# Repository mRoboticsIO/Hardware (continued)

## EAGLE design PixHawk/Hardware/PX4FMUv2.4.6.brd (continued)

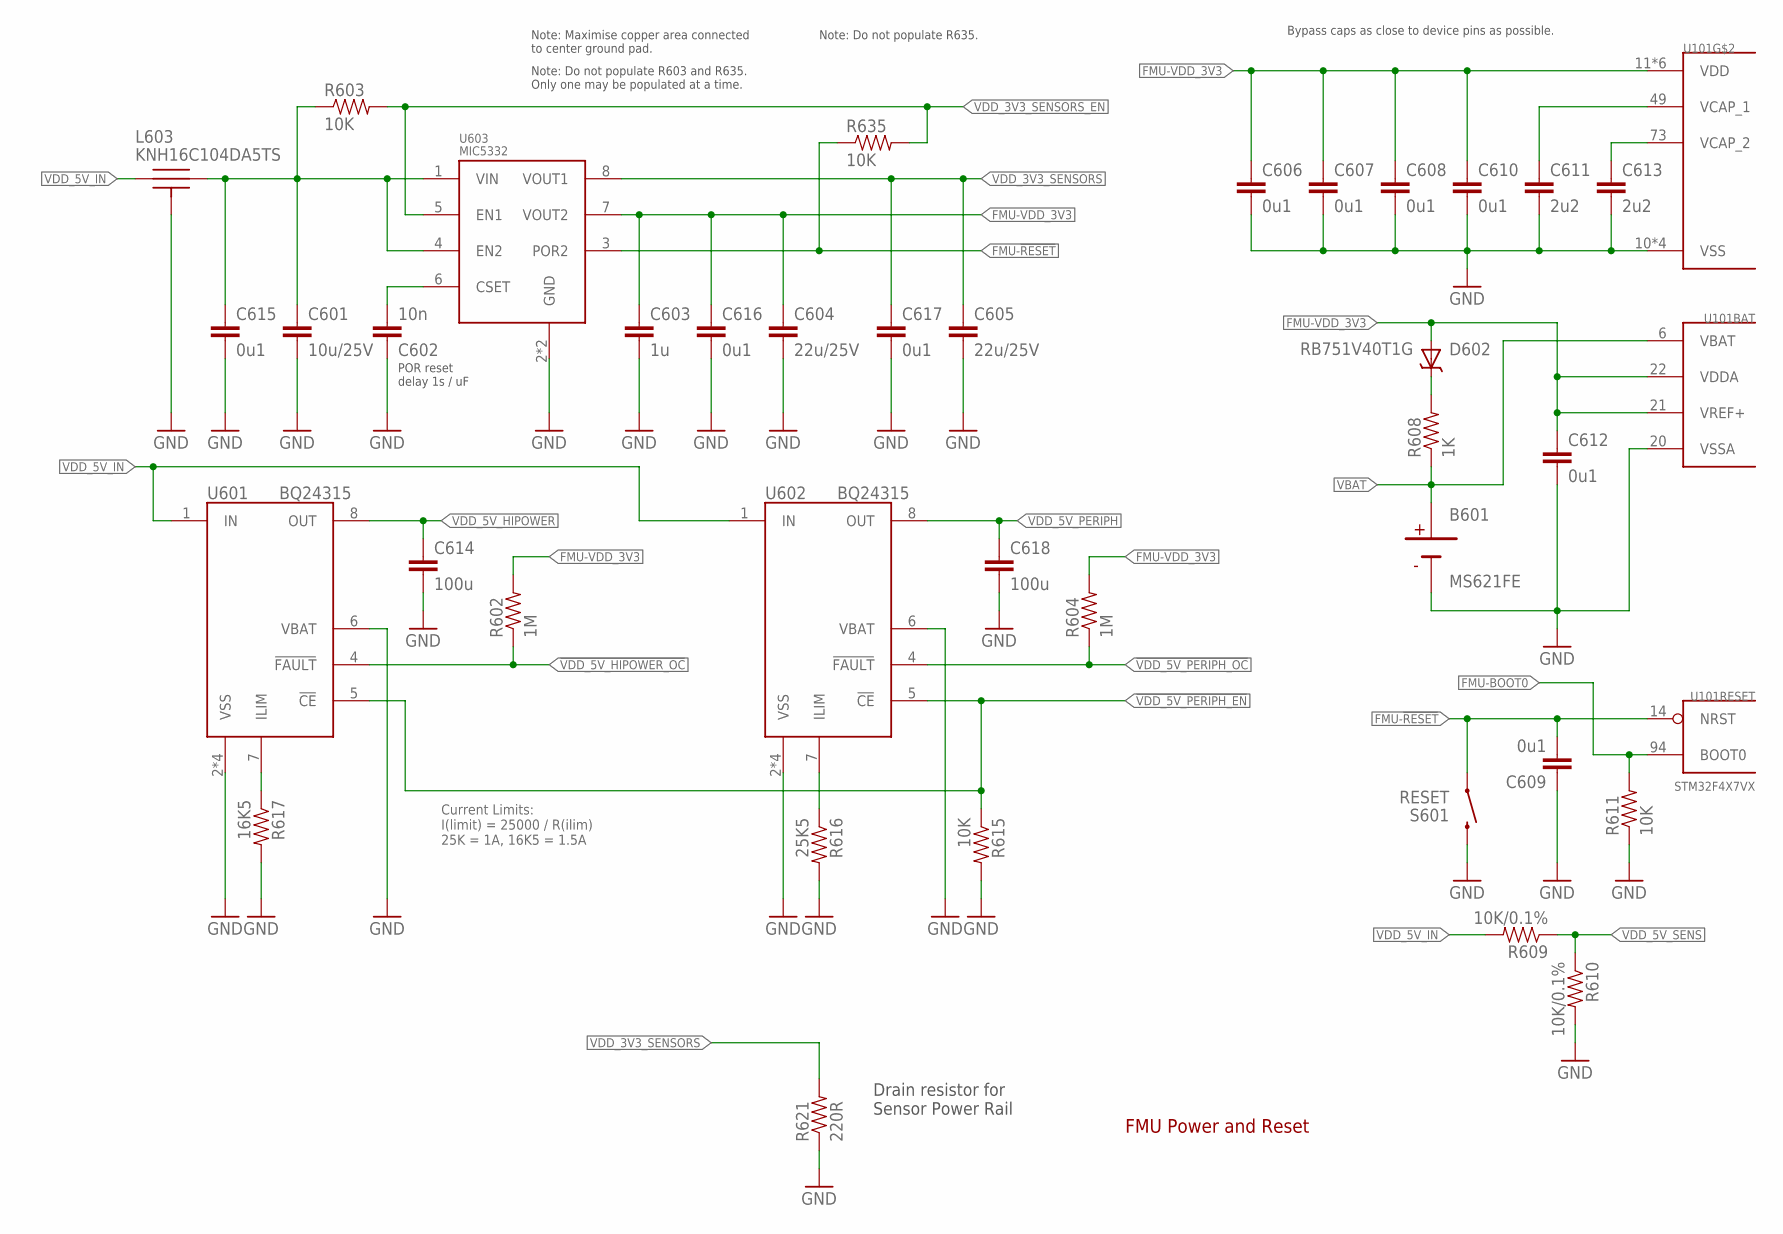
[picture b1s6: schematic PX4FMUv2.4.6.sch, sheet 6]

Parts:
B601: MS621FE; PARTNO MS621FE-FL11E
C601: 10u/25V; 0805-CAP; PARTNO CL21A106KAYNNNE
C602: 10n; 0402-CAP; PARTNO CC0402KRX7R7BB103
C603: 1u; 0603-CAP; PARTNO CC0603ZRY5V7BB105
C604, C605: 22u/25V; 0805-CAP; PARTNO CL21A226MAQNNNE
C606, C607, C608, C609, C610, C612, C615, C616, C617: 0u1; 0402-CAP; PARTNO CC0402ZRY5V7BB104
C611, C613: 2u2; 0603-CAP; PARTNO C1608X6S1C225K080AC
C614, C618: 100u; 1206-CAP; PARTNO C3216X5R1A107M160AC
D602: RB751V40T1G; SOD323; PARTNO RB751V40T1G
L603: KNH16C104DA5TS; KYOCERA-KNH16-DA; PARTNO KNH16C104DA5TS
R602, R604: 1M; 0402-RES; PARTNO RC0402FR-071ML
R603, R611, R615, R635: 10K; 0402-RES; PARTNO RC0402FR-0710KL
R608: 1K; 0402-RES; PARTNO RC0402FR-071KL
R609, R610: 10K/0.1%; 0402-RES; PARTNO ERA-2AEB103X
R616: 25K5; 0402-RES; PARTNO RMCF0402FT25K5
R617: 16K5; 0402-RES; PARTNO RMCF0402FT16K5
R621: 220R; 0603-RES; PARTNO RC1608J100CS
S601: RESET; EVQP7J01K; PARTNO EVQ-P7J01P
U101: STM32F4X7VX; TQFP100; PARTNO STM32F427VI
U601, U602: BQ24315; QFN8-DSG; PARTNO BQ24315DSGR
U603: MIC5332; MLF-8-EPAD; PARTNO MIC5332-SSYMT

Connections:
!VDD_5V_HIPOWER_OC: R602.P$1 (1), U601.4 (!FAULT); also elsewhere on the board
!VDD_5V_PERIPH_EN: R615.P$1 (1), U601.5 (!CE), U602.5 (!CE); also elsewhere on the board
!VDD_5V_PERIPH_OC: R604.P$1 (1), U602.4 (!FAULT); also elsewhere on the board
FMU-!RESET: C609.P$2 (2), R635.P$1 (1), S601.A1 (1), U101.14 (NRST), U603.3 (POR2); also elsewhere on the board
FMU-BOOT0: R611.P$2 (2), U101.94 (BOOT0); also elsewhere on the board
FMU-VDD_3V3: C603.P$1 (1), C604.P$1 (1), C606.P$1 (1), C607.P$1 (1), C608.P$1 (1), C610.P$1 (1), C612.P$1 (1), C616.P$1 (1), D602.A, R602.P$2 (2), R604.P$2 (2), U101.11 (VDD), U101.19 (VDD), U101.21 (VREF+), U101.22 (VDDA), U101.28 (VDD), U101.50 (VDD), U101.75 (VDD), U101.100 (VDD), U603.7 (VOUT2); also elsewhere on the board
FMU-VDD_5V5: C601.P$1 (1), C615.P$1 (1), L603.P$2, R603.P$1 (1), U603.1 (VIN), U603.4 (EN2)
GND: B601.2 (NEG), C601.P$2 (2), C602.P$1 (1), C603.P$2 (2), C604.P$2 (2), C605.P$2 (2), C606.P$2 (2), C607.P$2 (2), C608.P$2 (2), C609.P$1 (1), C610.P$2 (2), C611.P$2 (2), C612.P$2 (2), C613.P$2 (2), C614.P$2 (2), C615.P$2 (2), C616.P$2 (2), C617.P$2 (2), C618.P$2 (2), L603.P$3, L603.P$4, L603.P$5, R610.P$2 (2), R611.P$1 (1), R615.P$2 (2), R616.P$2 (2), R617.P$2 (2), R621.1, S601.B3 (2), U101.10 (VSS), U101.20 (VSSA), U101.27 (VSS), U101.74 (VSS), U101.99 (VSS), U601.2 (VSS), U601.6 (VBAT), U601.GND (VSS), U601.P$2 (VSS), U601.P$3 (VSS), U602.2 (VSS), U602.6 (VBAT), U602.GND (VSS), U602.P$2 (VSS), U602.P$3 (VSS), U603.2 (GND), U603.GND; also elsewhere on the board
unnamed: C613.P$1 (1), U101.73 (VCAP_2)
unnamed: C602.P$2 (2), U603.6 (CSET)
unnamed: C611.P$1 (1), U101.49 (VCAP_1)
unnamed: D602.C, R608.P$2 (2)
unnamed: R616.P$1 (1), U602.7 (ILIM)
unnamed: R617.P$1 (1), U601.7 (ILIM)
VBAT: B601.1 (POS), R608.P$1 (1), U101.6 (VBAT); also elsewhere on the board
VDD_3V3_SENSORS: C605.P$1 (1), C617.P$1 (1), R621.2, U603.8 (VOUT1); also elsewhere on the board
VDD_3V3_SENSORS_EN: R603.P$2 (2), R635.P$2 (2), U603.5 (EN1); also elsewhere on the board
VDD_5V_HIPOWER: C614.P$1 (1), U601.8 (OUT); also elsewhere on the board
VDD_5V_IN: L603.P$1, R609.P$2 (2), U601.1 (IN), U602.1 (IN); also elsewhere on the board
VDD_5V_PERIPH: C618.P$1 (1), U602.8 (OUT); also elsewhere on the board
VDD_5V_SENS: R609.P$1 (1), R610.P$1 (1); also elsewhere on the board

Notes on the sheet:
FMU Power and Reset
Bypass caps as close to device pins as possible.
Note: Maximise copper area connected to center ground pad.
POR reset delay 1s / uF
Current Limits: I(limit) = 25000 / R(ilim) 25K = 1A, 16K5 = 1.5A
Drain resistor for Sensor Power Rail
Note: Do not populate R603 and R635. Only one may be populated at a time.
Note: Do not populate R635.

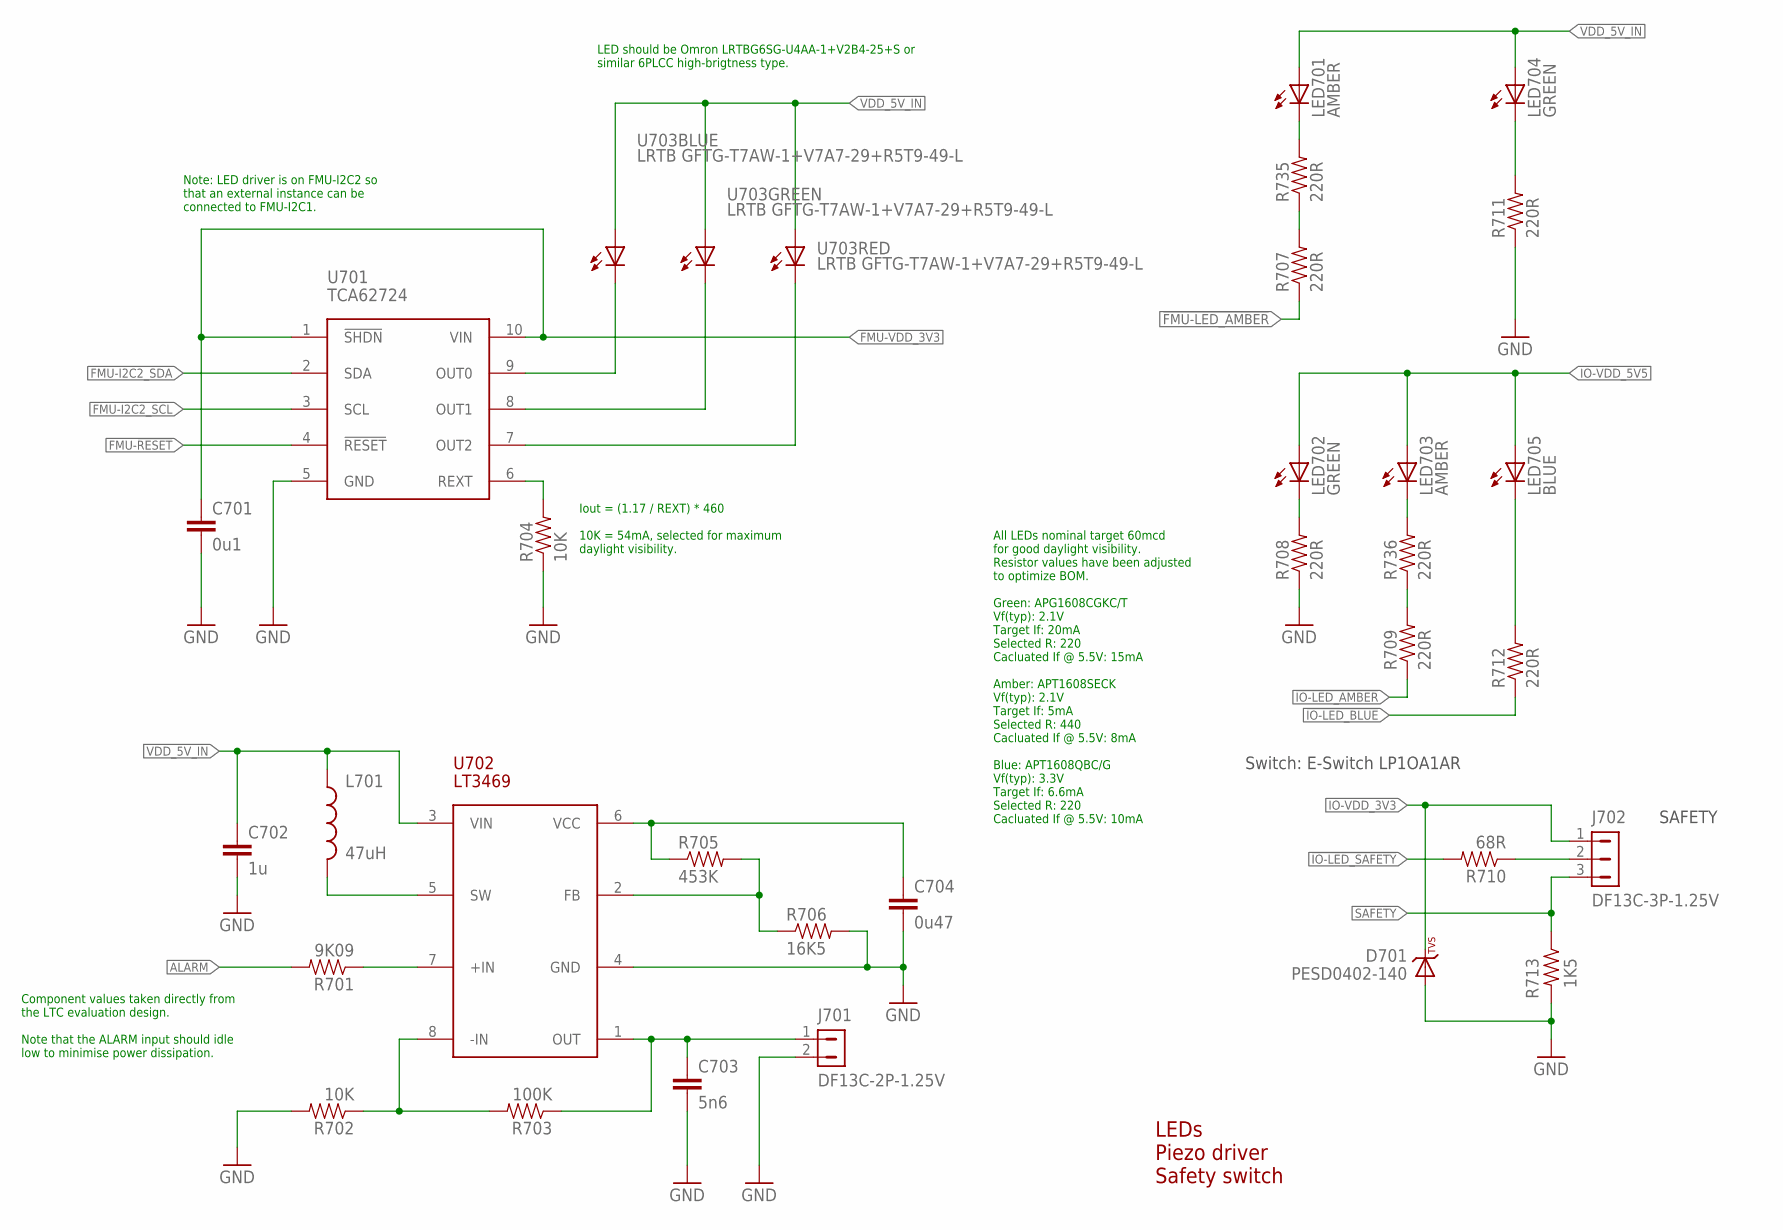
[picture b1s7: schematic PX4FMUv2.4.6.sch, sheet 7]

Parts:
C701: 0u1; 0402-CAP; PARTNO CC0402ZRY5V7BB104
C702: 1u; 0603-CAP; PARTNO CC0603ZRY5V7BB105
C703: 5n6; 0402-CAP; PARTNO C0402C562K5RACTU
C704: 0u47; 0402-CAP; PARTNO C1005X5R1C474K050BC
D701: PESD0402-140; 0402-TVS; PARTNO PESD0402-140
J701: DF13C-2P-1.25V; PARTNO DF13C-2P-1.25V(20)
J702: DF13C-3P-1.25V; PARTNO DF13C-3P-1.25V(20)
L701: 47uH; 0805-IND; PARTNO MLZ2012M470W
LED701, LED703: AMBER; 0603-LED; PARTNO APTD1608SECK
LED702, LED704: GREEN; 0603-LED; PARTNO APTD1608CGCK
LED705: BLUE; 0603-LED; PARTNO APTD1608QBC/D
R701: 9K09; 0402-RES; PARTNO RMCF0402FT9K09
R702, R704: 10K; 0402-RES; PARTNO RC0402FR-0710KL
R703: 100K; 0402-RES; PARTNO RC0402FR-07100KL
R705: 453K; 0402-RES; PARTNO RMCF0402FT453K
R706: 16K5; 0402-RES; PARTNO RMCF0402FT16K5
R707, R708, R709, R711, R712, R735, R736: 220R; 0402-RES; PARTNO RC0402FR-07220RL
R710: 68R; 0402-RES; PARTNO ERJ-2GEJ680X
R713: 1K5; 0402-RES; PARTNO RC0402FR-071K5L
U701: TCA62724FMG; SON10; PARTNO TCA62724FMG
U702: LT3469; SOT23-8; PARTNO LT3469ETS8
U703: LRTB GFTG-T7AW-1+V7A7-29+R5T9-49-L; 6-PLCC; PARTNO LRTB GFTG-T7AW-1+V7A7-29+R5T9-49-L

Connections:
!FMU-LED_AMBER: R707.P$1 (1); also elsewhere on the board
!IO-LED_AMBER: R709.P$1 (1); also elsewhere on the board
!IO-LED_BLUE: R712.P$1 (1); also elsewhere on the board
!IO-LED_SAFETY: R710.P$2 (2); also elsewhere on the board
ALARM: R701.P$2 (2); also elsewhere on the board
FMU-!RESET: U701.4 (!RESET); also elsewhere on the board
FMU-I2C2_SCL: U701.3 (SCL); also elsewhere on the board
FMU-I2C2_SDA: U701.2 (SDA); also elsewhere on the board
FMU-VDD_3V3: C701.P$1 (1), U701.1 (!SHDN), U701.10 (VIN); also elsewhere on the board
GND: C701.P$2 (2), C702.P$2 (2), C703.P$2 (2), C704.P$2 (2), D701.A, J701.2, R702.P$2 (2), R704.P$1 (1), R706.P$2 (2), R708.P$1 (1), R711.P$1 (1), R713.P$2 (2), U701.5 (GND), U702.4 (GND); also elsewhere on the board
IO-VDD_3V3: D701.C, J702.1; also elsewhere on the board
IO-VDD_5V5: LED702.A, LED703.A, LED705.A; also elsewhere on the board
unnamed: LED704.C, R711.P$2 (2)
unnamed: LED705.C, R712.P$2 (2)
unnamed: R707.P$2 (2), R735.P$1 (1)
unnamed: R705.P$2 (2), R706.P$1 (1), U702.2 (FB)
unnamed: R702.P$1 (1), R703.P$2 (2), U702.8 (-IN)
unnamed: LED701.C, R735.P$2 (2)
unnamed: C703.P$1 (1), J701.1, R703.P$1 (1), U702.1 (OUT)
unnamed: R701.P$1 (1), U702.7 (+IN)
unnamed: LED702.C, R708.P$2 (2)
unnamed: L701.P$2 (2), U702.5 (SW)
unnamed: C704.P$1 (1), R705.P$1 (1), U702.6 (VCC)
unnamed: R709.P$2 (2), R736.P$1 (1)
unnamed: LED703.C, R736.P$2 (2)
unnamed: J702.2, R710.P$1 (1)
unnamed: R704.P$2 (2), U701.6 (REXT)
RGB_LED_3: U701.9 (OUT0), U703.C1 (C)
RGB_LED_4: U701.8 (OUT1), U703.C2 (C)
RGB_LED_14: U701.7 (OUT2), U703.C3 (C)
SAFETY: J702.3, R713.P$1 (1); also elsewhere on the board
VDD_5V_IN: C702.P$1 (1), L701.P$1 (1), LED701.A, LED704.A, U702.3 (VIN), U703.A1 (A), U703.A2 (A), U703.A3 (A); also elsewhere on the board

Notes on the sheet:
LEDs Piezo driver Safety switch
Switch: E-Switch LP1OA1AR
SAFETY
LED should be Omron LRTBG6SG-U4AA-1+V2B4-25+S or similar 6PLCC high-brigtness type.
Iout = (1.17 / REXT) * 460 10K = 54mA, selected for maximum daylight visibility.
Note: LED driver is on FMU-I2C2 so that an external instance can be connected to FMU-I2C1.
All LEDs nominal target 60mcd for good daylight visibility. Resistor values have been adjusted to optimize BOM. Green: APG1608CGKC/T Vf(typ): 2.1V Target If: 20mA Selected R: 220 Cacluated If @ 5.5V: 15mA Amber: APT1608SECK Vf(typ): 2.1V Target If: 5mA Selected R: 440 Cacluated If @ 5.5V: 8mA Blue: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
Component values taken directly from the LTC evaluation design. Note that the ALARM input should idle low to minimise power dissipation.

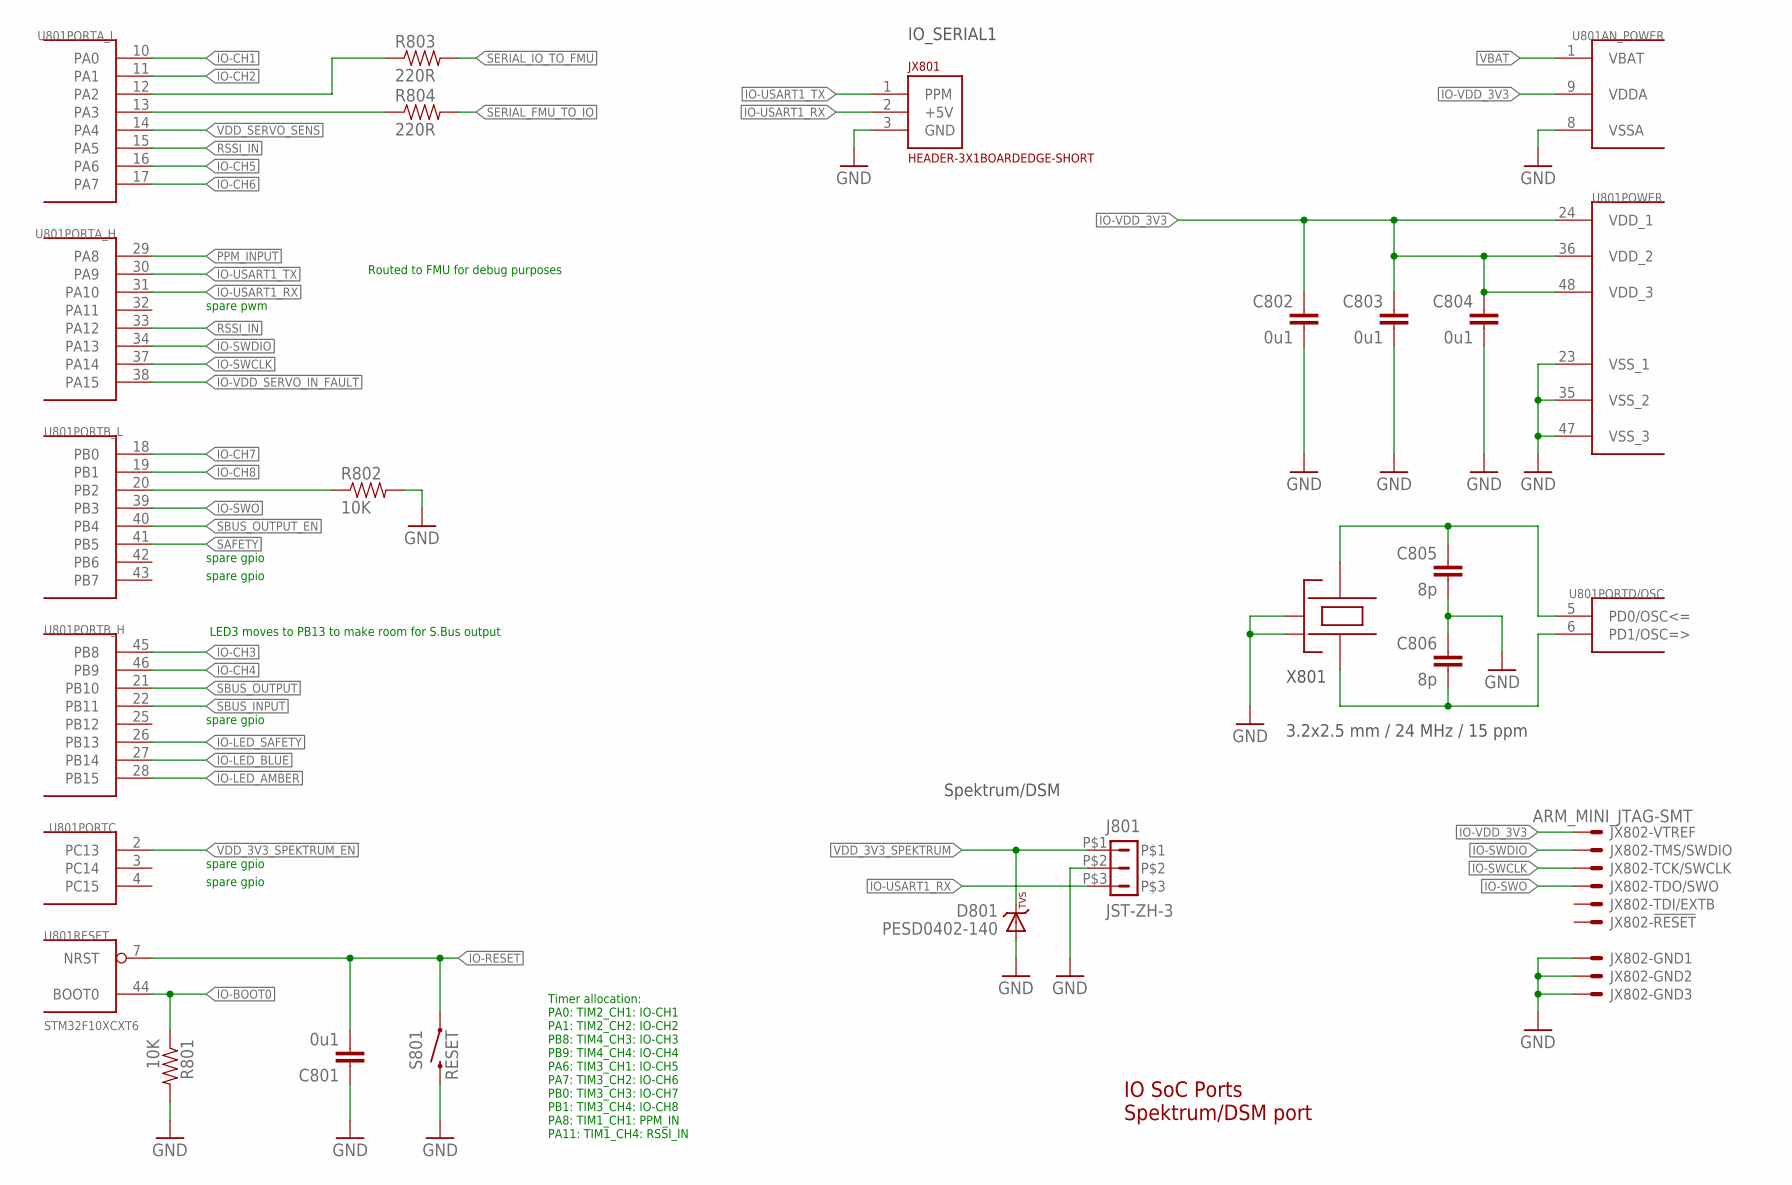
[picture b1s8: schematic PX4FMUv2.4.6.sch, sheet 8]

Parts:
C801, C802, C803, C804: 0u1; 0402-CAP; PARTNO CC0402ZRY5V7BB104
C805, C806: 8p; 0402-CAP; PARTNO C1005C0G1H080C
D801: PESD0402-140; 0402-TVS; PARTNO PESD0402-140
J801: JST-ZH-3; JST-ZH-SMT-VERTICAL; PARTNO B3B-ZR-SM4-TF (LF)(SN)(P)
JX801: HEADER-3X1BOARDEDGE-SHORT; HEADER_3X01_SMD_H_BOARD_EDGE_SHORT
JX802: ARM_MINI_JTAG-SMT; FTSH-105-01-XXX-DV-K; PARTNO M50-3900542
R801, R802: 10K; 0402-RES; PARTNO RC0402FR-0710KL
R803, R804: 220R; 0402-RES; PARTNO RC0402FR-07220RL
S801: RESET; EVQP7J01K; PARTNO EVQ-P7J01P
U801: STM32F10XCXT6; TQFP48; PARTNO STM32F100C8T6B
X801: 3.2x2.5 mm / 24 MHz / 15 ppm; OSCILLATOR-3.2X2.5; PARTNO NX3225SA-24.000000MHZ

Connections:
!IO-LED_AMBER: U801.28 (PB15); also elsewhere on the board
!IO-LED_BLUE: U801.27 (PB14); also elsewhere on the board
!IO-LED_SAFETY: U801.26 (PB13); also elsewhere on the board
!SBUS_OUTPUT_EN: U801.40 (PB4); also elsewhere on the board
GND: C801.P$1 (1), C802.P$2 (2), C803.P$2 (2), C804.P$2 (2), C805.P$2 (2), C806.P$1 (1), D801.A, J801.P$2, JX801.3 (GND), JX802.3, JX802.5, JX802.9, R801.P$2 (2), R802.P$2 (2), S801.B3 (2), U801.8 (VSSA), U801.23 (VSS_1), U801.35 (VSS_2), U801.47 (VSS_3), X801.2 (NC_2), X801.4 (NC_4); also elsewhere on the board
IO-!RESET: C801.P$2 (2), S801.A1 (1), U801.7 (NRST); also elsewhere on the board
IO-!VDD_SERVO_IN_FAULT: U801.38 (PA15); also elsewhere on the board
IO-BOOT0: R801.P$1 (1), U801.44 (BOOT0); also elsewhere on the board
IO-BOOT1: R802.P$1 (1), U801.20 (PB2)
IO-CH1: U801.10 (PA0); also elsewhere on the board
IO-CH2: U801.11 (PA1); also elsewhere on the board
IO-CH3: U801.45 (PB8); also elsewhere on the board
IO-CH4: U801.46 (PB9); also elsewhere on the board
IO-CH5: U801.16 (PA6); also elsewhere on the board
IO-CH6: U801.17 (PA7); also elsewhere on the board
IO-CH7: U801.18 (PB0); also elsewhere on the board
IO-CH8: U801.19 (PB1); also elsewhere on the board
IO-SWCLK: JX802.4, U801.37 (PA14)
IO-SWDIO: JX802.2, U801.34 (PA13)
IO-SWO: JX802.6, U801.39 (PB3)
IO-USART1_RX: J801.P$3, JX801.2 (+5V), U801.31 (PA10)
IO-USART1_TX: JX801.1 (PPM), U801.30 (PA9); also elsewhere on the board
IO-VDD_3V3: C802.P$1 (1), C803.P$1 (1), C804.P$1 (1), JX802.1, U801.9 (VDDA), U801.24 (VDD_1), U801.36 (VDD_2), U801.48 (VDD_3); also elsewhere on the board
unnamed: R803.P$1 (1), U801.12 (PA2)
unnamed: R804.P$1 (1), U801.13 (PA3)
unnamed: C806.P$2 (2), U801.6 (PD1/OSC=>), X801.1
unnamed: C805.P$1 (1), U801.5 (PD0/OSC<=), X801.3
PPM_INPUT: U801.29 (PA8); also elsewhere on the board
RSSI_IN: U801.15 (PA5), U801.33 (PA12); also elsewhere on the board
SAFETY: U801.41 (PB5); also elsewhere on the board
SBUS_INPUT: U801.22 (PB11); also elsewhere on the board
SBUS_OUTPUT: U801.21 (PB10); also elsewhere on the board
SERIAL_FMU_TO_IO: R804.P$2 (2); also elsewhere on the board
SERIAL_IO_TO_FMU: R803.P$2 (2); also elsewhere on the board
VBAT: U801.1 (VBAT); also elsewhere on the board
VDD_3V3_SPEKTRUM: D801.C, J801.P$1; also elsewhere on the board
VDD_3V3_SPEKTRUM_EN: U801.2 (PC13); also elsewhere on the board
VDD_SERVO_SENS: U801.14 (PA4); also elsewhere on the board

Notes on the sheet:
IO SoC Ports Spektrum/DSM port
LED3 moves to PB13 to make room for S.Bus output
Routed to FMU for debug purposes
IO_SERIAL1
Spektrum/DSM
Timer allocation: PA0: TIM2_CH1: IO-CH1 PA1: TIM2_CH2: IO-CH2 PB8: TIM4_CH3: IO-CH3 PB9: TIM4_CH4: IO-CH4 PA6: TIM3_CH1: IO-CH5 PA7: TIM3_CH2: IO-CH6 PB0: TIM3_CH3: IO-CH7 PB1: TIM3_CH4: IO-CH8 PA8: TIM1_CH1: PPM_IN PA11: TIM1_CH4: RSSI_IN
spare pwm
spare gpio

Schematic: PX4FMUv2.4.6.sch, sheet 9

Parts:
C901, C902, C903: 0u1; 0402-CAP; PARTNO CC0402ZRY5V7BB104
D901, D902, D903: PESD0402-140; 0402-TVS; PARTNO PESD0402-140
D904: MSS1P4-M3; MICROSMP; PARTNO MSS1P4-M3/89A
J901: HEADER-3X163X16RA; 3X16RA
L901: KNH16C104DA5TS; KYOCERA-KNH16-DA; PARTNO KNH16C104DA5TS
R901: 10K; 0402-RES; PARTNO RC0402FR-0710KL
R902, R903, R904, R905, R906, R907, R908, R909, R910, R911, R912, R913, R914, R915, R916, R917: 220R; 0402-RES; PARTNO RC0402FR-07220RL
R918, R919, R922: 10K/0.1%; 0402-RES; PARTNO ERA-2AEB103X
U901, U902: TXS0108QFN20; QFN20-RGY; PARTNO TXS0108ERGYR
U903: 74LVC2G240; TSSOP8_SOT505-2; PARTNO 74LVC2G240DP,125

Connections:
!SBUS_OUTPUT_EN: U903.7 (!2OE); also elsewhere on the board
FMU-CH1: U901.7 (A6); also elsewhere on the board
FMU-CH1-PROT: J901.46, R913.P$2 (2)
FMU-CH2: U901.6 (A5); also elsewhere on the board
FMU-CH3: U901.5 (A4); also elsewhere on the board
FMU-CH4: U901.4 (A3); also elsewhere on the board
FMU-CH5: U901.3 (A2); also elsewhere on the board
FMU-CH6: U901.1 (A1); also elsewhere on the board
FMU-CH6-PROT: J901.31, R902.P$2 (2)
FMU-VDD_3V3: C902.P$1 (1), U901.2 (VCCA), U901.10 (OE), U901.19 (VCCB); also elsewhere on the board
GND: C901.P$2 (2), C902.P$2 (2), C903.P$2 (2), D901.A, D902.A, D903.A, J901.3, J901.6, J901.9, J901.12, J901.15, J901.18, J901.21, J901.24, J901.27, J901.30, J901.33, J901.36, J901.39, J901.42, J901.45, J901.48, L901.P$3, L901.P$4, L901.P$5, R919.P$1 (1), U901.11 (GND), U902.11 (GND), U903.1 (!1OE), U903.4 (GND); also elsewhere on the board
IO-CH1: U902.9 (A8); also elsewhere on the board
IO-CH1-PROT: J901.28, R917.P$2 (2)
IO-CH2: U902.8 (A7); also elsewhere on the board
IO-CH3: U902.7 (A6); also elsewhere on the board
IO-CH4: U902.6 (A5); also elsewhere on the board
IO-CH5: U902.5 (A4); also elsewhere on the board
IO-CH6: U902.4 (A3); also elsewhere on the board
IO-CH7: U902.3 (A2); also elsewhere on the board
IO-CH8: U902.1 (A1); also elsewhere on the board
IO-CH8-PROT: J901.7, R905.P$2 (2)
IO-VDD_3V3: C901.P$1 (1), C903.P$1 (1), U902.2 (VCCA), U902.10 (OE), U902.19 (VCCB), U903.8 (VCC); also elsewhere on the board
IO-VDD_5V5: J901.2; also elsewhere on the board
unnamed: R918.P$2 (2), R922.P$1 (1)
unnamed: J901.10, R914.P$2 (2)
unnamed: D902.C, R901.P$2 (2), R910.P$1 (1), U903.3 (2Y)
unnamed: R905.P$1 (1), U902.20 (B1)
unnamed: R914.P$1 (1), U902.18 (B2)
unnamed: R906.P$1 (1), U902.17 (B3)
unnamed: R915.P$1 (1), U902.16 (B4)
unnamed: R907.P$1 (1), U902.15 (B5)
unnamed: R916.P$1 (1), U902.14 (B6)
unnamed: R908.P$1 (1), U902.13 (B7)
unnamed: R917.P$1 (1), U902.12 (B8)
unnamed: R902.P$1 (1), U901.20 (B1)
unnamed: R911.P$1 (1), U901.18 (B2)
unnamed: R903.P$1 (1), U901.17 (B3)
unnamed: R912.P$1 (1), U901.16 (B4)
unnamed: R904.P$1 (1), U901.15 (B5)
unnamed: R913.P$1 (1), U901.14 (B6)
unnamed: J901.34, R911.P$2 (2)
unnamed: J901.13, R906.P$2 (2)
unnamed: J901.16, R915.P$2 (2)
unnamed: J901.19, R907.P$2 (2)
unnamed: J901.22, R916.P$2 (2)
unnamed: J901.25, R908.P$2 (2)
unnamed: J901.37, R903.P$2 (2)
unnamed: J901.40, R912.P$2 (2)
unnamed: J901.43, R904.P$2 (2)
unnamed: J901.4, R910.P$2 (2)
unnamed: D903.C, D904.CATHODE (C), L901.P$1
PPM-SBUS-PROT: J901.1, R909.P$2 (2)
PPM_INPUT: D901.C, R909.P$1 (1), U903.2 (1A); also elsewhere on the board
RSSI_IN: R901.P$1 (1); also elsewhere on the board
SBUS_INPUT: U903.6 (1Y); also elsewhere on the board
SBUS_OUTPUT: U903.5 (2A); also elsewhere on the board
VDD_SERVO: D904.ANODE (A), J901.5, J901.8, J901.11, J901.14, J901.17, J901.20, J901.23, J901.26, J901.29, J901.32, J901.35, J901.38, J901.41, J901.44, J901.47, R922.P$2 (2); also elsewhere on the board
VDD_SERVO_IN: L901.P$2; also elsewhere on the board
VDD_SERVO_SENS: R918.P$1 (1), R919.P$2 (2); also elsewhere on the board

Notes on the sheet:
Servo Header S.Bus interface
S.Bus in/out
Servo outputs

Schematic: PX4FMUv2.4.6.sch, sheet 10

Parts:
C1001: 10u/25V; 0805-CAP; PARTNO CL21A106KAYNNNE
C1002: 10n; 0402-CAP; PARTNO CC0402KRX7R7BB103
C1003: 1u; 0603-CAP; PARTNO CC0603ZRY5V7BB105
C1004: 10u; 0603-CAP; PARTNO C1608X5R1A106K080AC
C1005: 0u1; 0402-CAP; PARTNO CC0402ZRY5V7BB104
C1008: 2u2; 0402-CAP; PARTNO C1005X6S1C225K050BC
D1001: PMEG2005CT; SOT23-3; PARTNO PMEG2005CT
F1001: 0ZCA0035FF2G; PTC-1206; PARTNO 0ZCA0035FF2G
R1001: 100K; 0402-RES; PARTNO RC0402FR-07100KL
R1002: 10K; 0402-RES; PARTNO RC0402FR-0710KL
U1001: BQ24313; QFN8-DSG; PARTNO BQ24313DSGT
U1002: MIC5332; MLF-8-EPAD; PARTNO MIC5332-SSYMT

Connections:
GND: C1001.P$2 (2), C1002.P$2 (2), C1003.P$2 (2), C1004.P$2 (2), C1005.P$2 (2), C1008.P$2 (2), R1001.P$1 (1), R1002.P$1 (1), U1001.2 (VSS), U1001.5 (!CE), U1001.6 (VBAT), U1001.GND (VSS), U1001.P$2 (VSS), U1001.P$3 (VSS), U1002.2 (GND), U1002.GND; also elsewhere on the board
IO-!RESET: U1002.3 (POR2); also elsewhere on the board
IO-!VDD_SERVO_IN_FAULT: U1001.4 (!FAULT); also elsewhere on the board
IO-VDD_3V3: C1003.P$1 (1), C1004.P$1 (1), U1002.7 (VOUT2); also elsewhere on the board
IO-VDD_5V5: C1001.P$1 (1), C1005.P$1 (1), D1001.3 (CC), U1002.1 (VIN), U1002.4 (EN2); also elsewhere on the board
unnamed: D1001.2 (A2), U1001.8 (OUT)
unnamed: R1001.P$2 (2), U1001.7 (ILIM)
unnamed: D1001.1 (A1), F1001.2
unnamed: C1002.P$1 (1), U1002.6 (CSET)
VDD_3V3_SPEKTRUM: C1008.P$1 (1), U1002.8 (VOUT1); also elsewhere on the board
VDD_3V3_SPEKTRUM_EN: R1002.P$2 (2), U1002.5 (EN1); also elsewhere on the board
VDD_5V_IN: F1001.1; also elsewhere on the board
VDD_SERVO_IN: U1001.1 (IN); also elsewhere on the board

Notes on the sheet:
Dual supply from servo rail and FMU 5V rail
Current limit = 25 / Rilim (current in A, R in kOhms) 100K = 250mA
IO Power Supply
Reset output 1s / uF 10n = 10ms delay from power good to reset de-asserted.
Output voltage limited to 5.5V for input voltages up to 10.5V; output switches off at higher input voltages.

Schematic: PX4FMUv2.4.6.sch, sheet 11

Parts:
C1101, C1102, C1103: 22u/25V; 0805-CAP; PARTNO CL21A226MAQNNNE
C1104: 100u; 1206-CAP; PARTNO C3216X5R1A107M160AC
C1105, C1106, C1107: 0u1; 0402-CAP; PARTNO C1005X7R1E104K050BB
C1108, C1109, C1110: 10p/25V; 0402-CAP; PARTNO C0402C100J3GACTU
J601: DF13C-6P-1.25V; PARTNO DF13C-6P-1.25V(20)
L1101, L1102: KNH16C104DA5TS; KYOCERA-KNH16-DA; PARTNO KNH16C104DA5TS
R1101, R1102: 10K/0.1%; 0402-RES; PARTNO ERA-2AEB103X
R1103, R1104: 1M; 0402-RES; PARTNO RC0402FR-071ML
R1105, R1109, R1112: 453K; 0402-RES; PARTNO RMCF0402FT453K
R1106, R1110, R1113: 56K; 0402-RES; PARTNO ERA-2AEB563X
R1107, R1111, R1114: 105K; 0402-RES; PARTNO ERJ-2RKF1053X
R1115: 0R; 0402-RES; PARTNO ERJ-2GE0R00X
RN1101: 1M; EXB28V; PARTNO EXB-28V105JX
U1101: LTC4417; MO-220; PARTNO LTC4417IUF#PBF
U1102, U1103, U1104: NTHD4102PT1G; 1206-8; PARTNO NTHD4102PT1G

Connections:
!VBUS_VALID: RN1101.2 (1), U1101.P$9 (!VALID3); also elsewhere on the board
!VDD_BRICK_VALID: RN1101.4 (1), U1101.P$7 (!VALID1); also elsewhere on the board
!VDD_SERVO_VALID: RN1101.3 (1), U1101.P$8 (!VALID2); also elsewhere on the board
BATT_CURRENT_SENS: R1101.P$1 (1); also elsewhere on the board
BATT_CURRENT_SENS_PROT: J601.3, L1101.P$1, R1104.P$1 (1)
BATT_VOLTAGE_SENS: R1102.P$1 (1); also elsewhere on the board
BATT_VOLTAGE_SENS_PROT: J601.4, L1102.P$1, R1103.P$1 (1)
GND: C1101.P$2 (2), C1102.P$2 (2), C1103.P$2 (2), C1104.P$2 (2), C1105.P$2 (2), C1106.P$2 (2), C1107.P$2 (2), C1108.P$2 (2), C1109.P$2 (2), C1110.P$2 (2), J601.5, J601.6, L1101.P$3, L1101.P$4, L1101.P$5, L1102.P$3, L1102.P$4, L1102.P$5, R1103.P$2 (2), R1104.P$2 (2), R1107.P$2 (2), R1111.P$2 (2), R1114.P$2 (2), R1115.P$1 (1), U1101.P$10 (GND), U1101.P$25 (GND); also elsewhere on the board
unnamed: C1108.P$1 (1), R1105.P$2 (2), R1106.P$1 (1), U1101.P$1 (UV1)
unnamed: R1106.P$2 (2), R1107.P$1 (1), U1101.P$2 (OV1)
unnamed: C1109.P$1 (1), R1109.P$2 (2), R1110.P$1 (1), U1101.P$3 (UV2)
unnamed: R1110.P$2 (2), R1111.P$1 (1), U1101.P$4 (OV2)
unnamed: R1113.P$2 (2), R1114.P$1 (1), U1101.P$6 (OV3)
unnamed: C1110.P$1 (1), R1112.P$2 (2), R1113.P$1 (1), U1101.P$5 (UV3)
unnamed: C1105.P$1 (1), U1101.P$18 (VS1), U1102.P$1 (S), U1102.P$3 (S)
unnamed: L1102.P$2, R1102.P$2 (2)
unnamed: L1101.P$2, R1101.P$2 (2)
unnamed: R1115.P$2 (2), U1101.P$24 (HYS)
unnamed: C1106.P$1 (1), U1101.P$16 (VS2), U1103.P$1 (S), U1103.P$3 (S)
unnamed: C1107.P$1 (1), U1101.P$14 (VS3), U1104.P$1 (S), U1104.P$3 (S)
unnamed: U1101.P$13 (G3), U1104.P$2 (G), U1104.P$4 (G)
unnamed: U1101.P$15 (G2), U1103.P$2 (G), U1103.P$4 (G)
unnamed: U1101.P$17 (G1), U1102.P$2 (G), U1102.P$4 (G)
VBUS: C1103.P$1 (1), R1112.P$1 (1), U1101.P$19 (V3), U1104.P$7 (D), U1104.P$8 (D); also elsewhere on the board
VDD_5V_BRICK: C1101.P$1 (1), J601.1, J601.2, R1105.P$1 (1), U1101.P$21 (V1), U1102.P$7 (D), U1102.P$8 (D); also elsewhere on the board
VDD_5V_IN: C1104.P$1 (1), RN1101.5 (2), RN1101.6 (2), RN1101.7 (2), U1101.P$12 (VOUT), U1102.P$5 (D), U1102.P$6 (D), U1103.P$5 (D), U1103.P$6 (D), U1104.P$5 (D), U1104.P$6 (D); also elsewhere on the board
VDD_SERVO: C1102.P$1 (1), R1109.P$1 (1), U1101.P$20 (V2), U1103.P$7 (D), U1103.P$8 (D); also elsewhere on the board

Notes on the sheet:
Power source selector
Resistors picked so that undervoltage lockout starts at 4.0V and overvoltage lockout at 5.75V. Use 1% or better accuracy!
POWER PATH CONTROLLER: Does enable output if valid for continous 256 ms
XXX Check all input pins are 5V tolerant. Hooking this up to a 3.3V rail would make the lines non-readable during power-up sequencing

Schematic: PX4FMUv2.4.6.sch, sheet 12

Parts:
!VBUS_VALID: PAD.04; PAD.04X.04; PARTNO *
!VDD_BRICK_VALID: PAD.04; PAD.04X.04; PARTNO *
!VDD_SERVO_VALID: PAD.04; PAD.04X.04; PARTNO *
ADC_PR: PAD.04; PAD.04X.04; PARTNO *
CAN_H: PAD.04; PAD.04X.04; PARTNO *
CAN_L: PAD.04; PAD.04X.04; PARTNO *
FMU-BOOT1101: PAD.04; PAD.04X.04; PARTNO *
GND, GND.: PAD.04; PAD.04X.04; PARTNO *
IO-BOOT1101: PAD.04; PAD.04X.04; PARTNO *
JP1, JP2: FIDUCIAL1.5X3; FIDUCIAL-1.5X3; PARTNO *
M3_MOUNT1101, M3_MOUNT1102, M3_MOUNT1103, M3_MOUNT1104: MOUNT-HOLE3.1MM; MOUNT-HOLE3.1; PARTNO *
OSHW_LOGO: OSHW-LOGOS; OSHW-LOGO-S; PARTNO *
S1RX, S1TX, S2RX, S2TX, S3RX, S3TX, S4RX, S4TX, S5_RX, S5_TX: PAD.04; PAD.04X.04; PARTNO *
VBUS: PAD.04; PAD.04X.04; PARTNO *
VDDA_3V1101: PAD.04; PAD.04X.04; PARTNO *
VDD_3V1101, VDD_5V_BRICK, VDD_5V_IN: PAD.04; PAD.04X.04; PARTNO *
VDD_SERVO: PAD.04; PAD.04X.04; PARTNO *

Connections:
!VBUS_VALID: !VBUS_VALID.P$1; also elsewhere on the board
!VDD_BRICK_VALID: !VDD_BRICK_VALID.P$1; also elsewhere on the board
!VDD_SERVO_VALID: !VDD_SERVO_VALID.P$1; also elsewhere on the board
CAN_H: CAN_H.P$1; also elsewhere on the board
CAN_L: CAN_L.P$1; also elsewhere on the board
FMU-BOOT0: FMU-BOOT1101.P$1; also elsewhere on the board
FMU-VDD_3V3: VDD_3V1101.P$1; also elsewhere on the board
GND: GND.P$1, GND..P$1; also elsewhere on the board
IO-BOOT0: IO-BOOT1101.P$1; also elsewhere on the board
PRESSURE_SENS_IN: ADC_PR.P$1; also elsewhere on the board
SERIAL1_RX: S1RX.P$1; also elsewhere on the board
SERIAL1_TX: S1TX.P$1; also elsewhere on the board
SERIAL2_RX: S2RX.P$1; also elsewhere on the board
SERIAL2_TX: S2TX.P$1; also elsewhere on the board
SERIAL3_RX: S3RX.P$1; also elsewhere on the board
SERIAL3_TX: S3TX.P$1; also elsewhere on the board
SERIAL4_RX: S4RX.P$1; also elsewhere on the board
SERIAL4_TX: S4TX.P$1; also elsewhere on the board
SERIAL5_RX: S5_RX.P$1; also elsewhere on the board
SERIAL5_TX: S5_TX.P$1; also elsewhere on the board
VBUS: VBUS.P$1; also elsewhere on the board
VDD_3V3_SENSORS: VDDA_3V1101.P$1; also elsewhere on the board
VDD_5V_BRICK: VDD_5V_BRICK.P$1; also elsewhere on the board
VDD_5V_IN: VDD_5V_IN.P$1; also elsewhere on the board
VDD_SERVO: VDD_SERVO.P$1; also elsewhere on the board

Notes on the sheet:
Mounting holes to suit M3 fastener
and Richco R908 series spacer.
Use R908-5 spacers to stack with
other PX4 series boards (7.95 mm).
Production Testing Pads
Test and Fiducials
Minimum drill: 0.3 mm
Minimum trace width (use mm for traces): 0.15 mm
Minimum copper distance (all signals): 0.15 mm
Dimension / hole minimum distance: 0.2 mm
Layout grid: 4 mil, part grid: 4 mil. Dimensions / hole positions: 0.5 mm
Board: FR4 black, 1.0 mm. Solder stop on vias < 0.6 mm.
Signoff rules: Footprint checked, pinmap checked, schematic checked, cross-references to other pages checked.
Routing: 1: general/escape 2: ground 3: horizontal 4: vertical 5: power 6: general/escape
Fiducials for machine vision alignment.
Parts: Resistors: 0402 / 1% unless specified otherwise Capacitors: 0402 to 1206, ceramic, voltage rating: 10V unless specified
COMMS
POWER
STATUS AND ANALOG

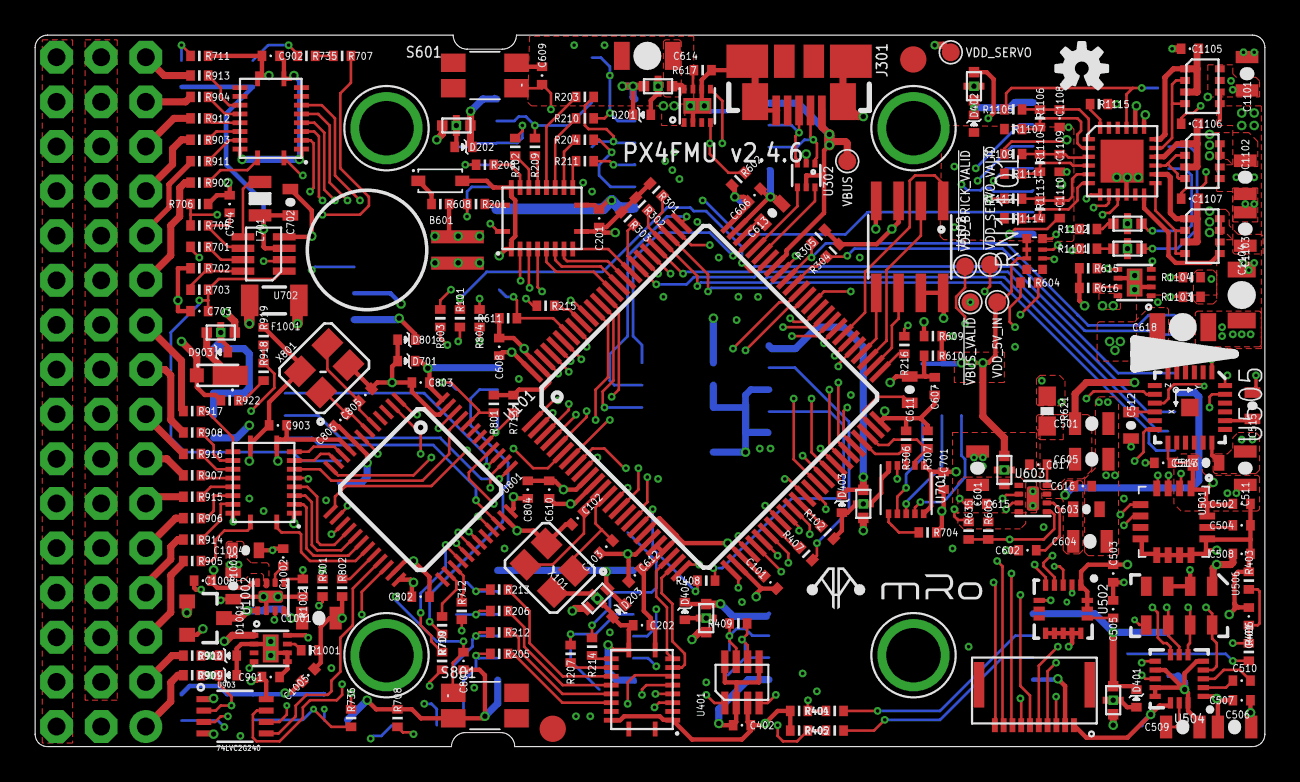
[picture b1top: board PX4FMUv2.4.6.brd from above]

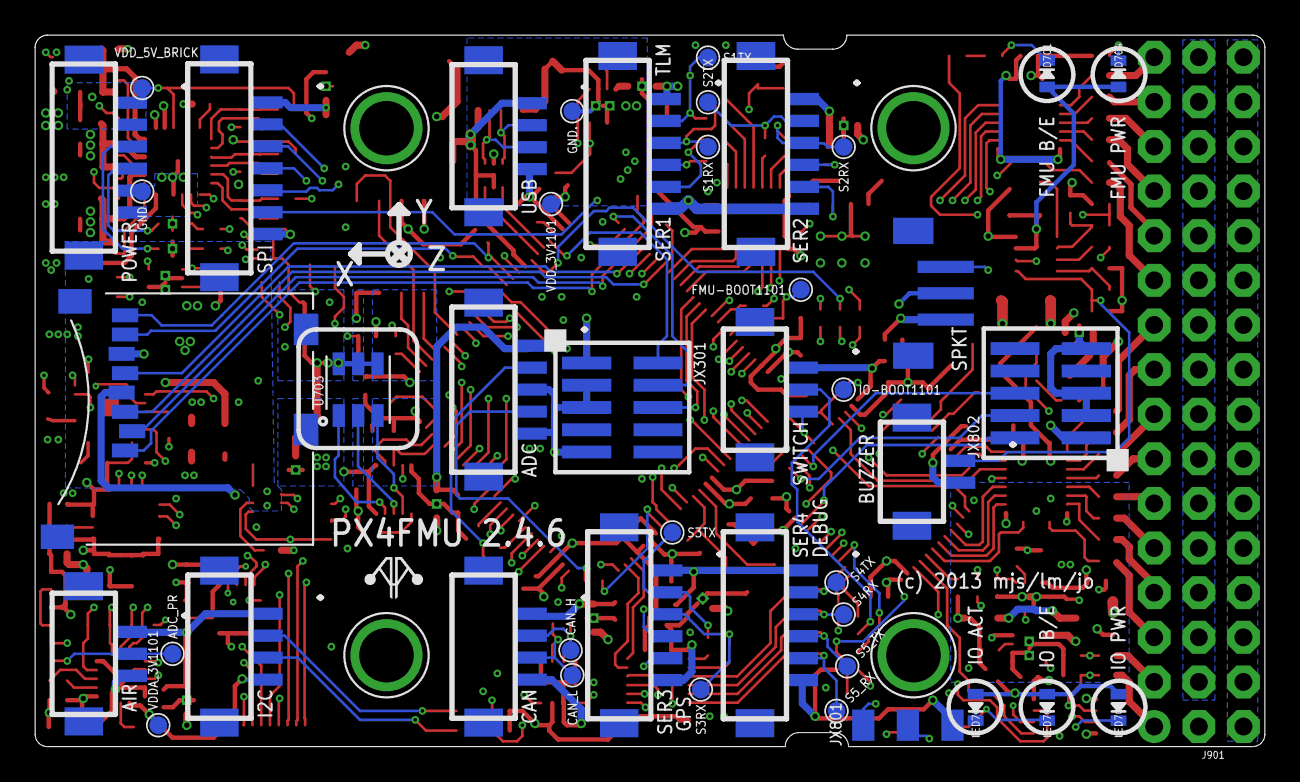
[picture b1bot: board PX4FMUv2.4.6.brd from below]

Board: 6 copper layers, 70.0 x 40.5 mm, 290 parts (45 on the bottom side), 260 nets.

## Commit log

2017-10-30 testing
2017-10-30 Added PixHawk
2017-10-30 added pixracer hw diagram
2017-11-06 Update
    updating files
2017-11-06 Updated datasheet
2017-11-06 Added more pictures
2017-11-06 Added pic
2017-11-06 updated pics
2017-11-10 Correct everything
    Ready for release?
2017-11-17 Correction
    Corrected CAN BUS pin outs.
2017-11-28 Adding BL Update tool
2018-04-10 GPS Drawing Update
2018-07-23 X2.1 Wiki Updates
    Added new instructions to update the proper X2.1 bootloader.
